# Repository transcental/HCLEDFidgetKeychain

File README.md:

# Hack Club LED Fidget Keychain

For my [Solder](https://solder.hackclub.com) project, I decided to make a keychain that has LEDs arranged into the Hack Club "h" logo. The LEDs turn on when it gets dark, and turn off when it's light, using a photoresistor. The design also features a button controller vibration motor for maximum fidgeting ability.

## Parts List
- 1x PCB
- 6x LEDs
- 6x 220Ω resistors
- 3x 4.7kΩ resistors
- 1x Photoresistor
- 1x Push button
- 1x Vibration motor
- 1x CR2032 battery holder
- 1x CR2032 battery
- 1x NPN transistor

## Images

### Schematic

### PCB

### 3D Model

_Made by Amber - @transcental on Slack_

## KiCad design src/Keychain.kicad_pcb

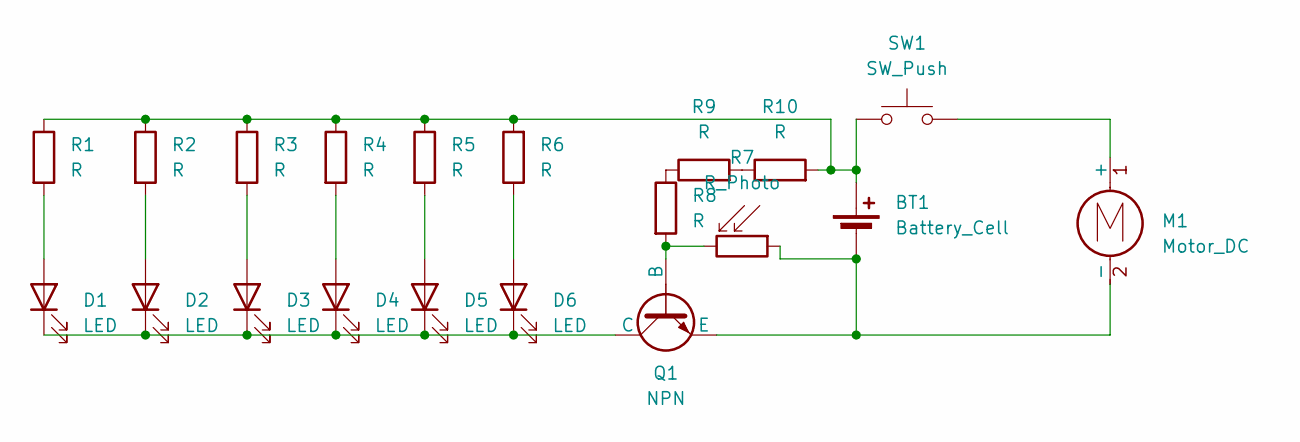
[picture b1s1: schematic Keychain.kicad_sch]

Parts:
BT1: Battery_Cell; BatteryHolder_Keystone_3034_1x20mm
D1, D2, D3, D4, D5, D6: LED; LED_D5.0mm
M1: Motor_DC; PinHeader_2x01_P2.54mm_Vertical
Q1: NPN; TO-92L_HandSolder
R1, R2, R3, R4, R5, R6, R8, R9, R10: R; R_Axial_DIN0207_L6.3mm_D2.5mm_P7.62mm_Horizontal
R7: R_Photo; R_LDR_5.1x4.3mm_P3.4mm_Vertical
SW1: SW_Push; SW_PUSH_6mm

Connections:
unnamed: BT1.1 (+), R1.1, R2.1, R3.1, R4.1, R5.1, R6.2, R10.2, SW1.1
unnamed: BT1.2 (-), M1.2 (-), Q1.3 (E), R7.1
unnamed: D1.2 (A), R1.2
unnamed: D1.1 (K), D2.1 (K), D3.1 (K), D4.1 (K), D5.1 (K), D6.1 (K), Q1.1 (C)
unnamed: D2.2 (A), R2.2
unnamed: D3.2 (A), R3.2
unnamed: D4.2 (A), R4.2
unnamed: D5.2 (A), R5.2
unnamed: D6.2 (A), R6.1
unnamed: M1.1 (+), SW1.2
unnamed: Q1.2 (B), R7.2, R8.2
unnamed: R8.1, R9.1
unnamed: R9.2, R10.1

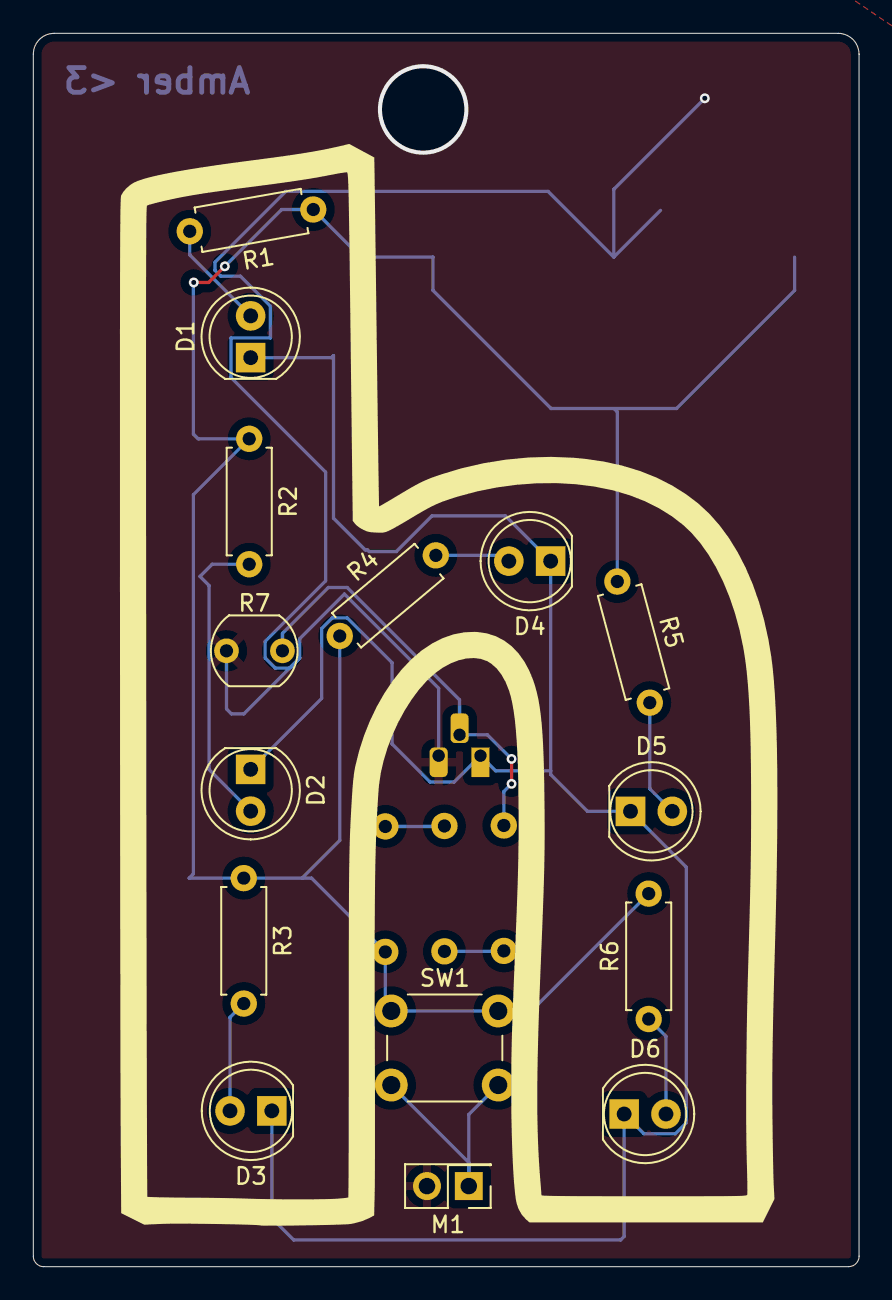
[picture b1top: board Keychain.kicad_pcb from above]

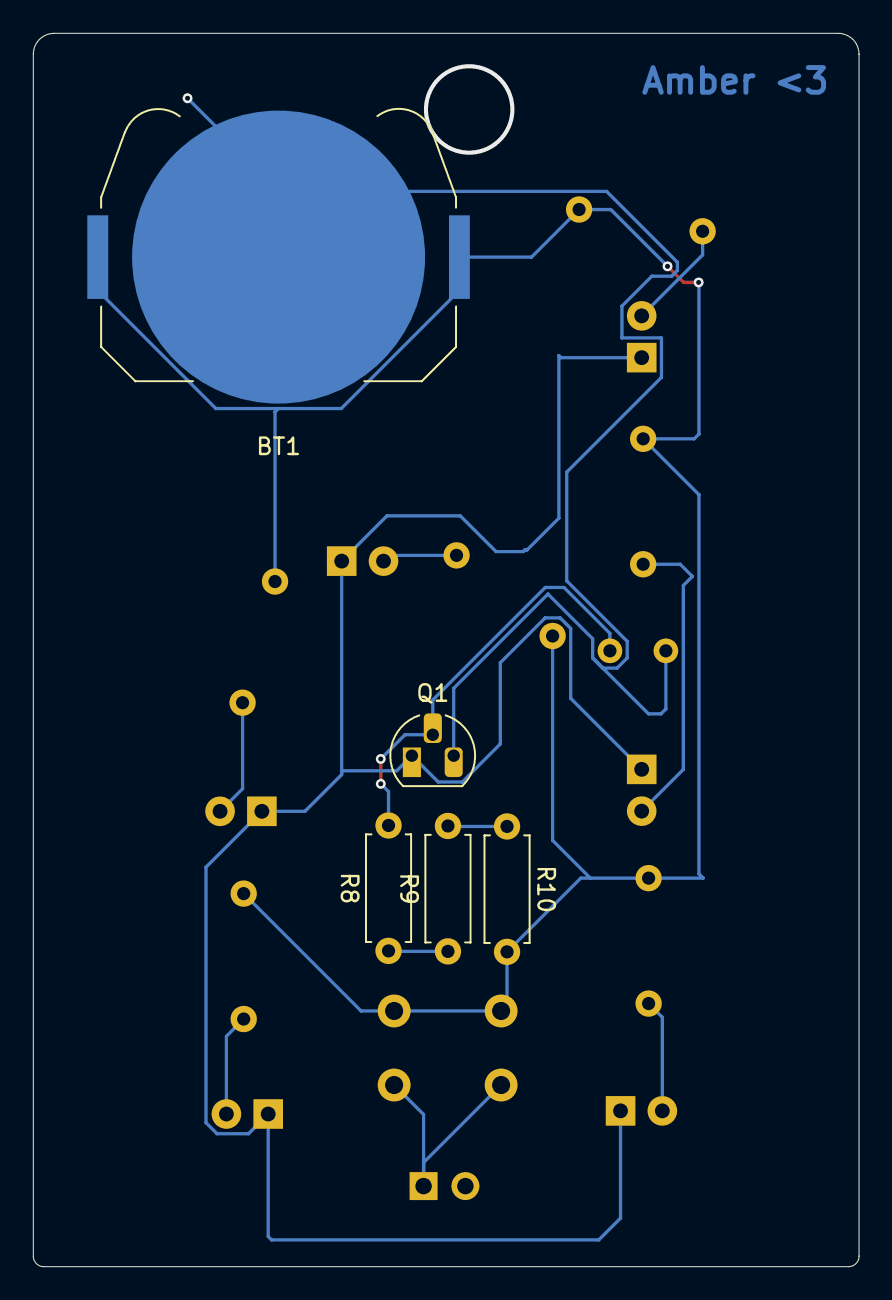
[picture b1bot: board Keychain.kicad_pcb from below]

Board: 2 copper layers, 50.2 x 74.9 mm, 20 parts (5 on the bottom side), 13 nets.

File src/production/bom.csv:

Designator,Footprint,Quantity,Value,LCSC Part #
BT1,BatteryHolder_Keystone_3034_1x20mm,1,Battery_Cell,
"D1, D2, D3, D4, D5, D6",LED_D5.0mm,6,LED,
M1,PinHeader_2x01_P2.54mm_Vertical,1,Motor_DC,
Q1,TO-92L_HandSolder,1,NPN,
"R1, R10, R2, R3, R4, R5, R6, R8, R9",R_Axial_DIN0207_L6.3mm_D2.5mm_P7.62mm_Horizontal,9,R,
R7,R_LDR_5.1x4.3mm_P3.4mm_Vertical,1,R_Photo,
SW1,SW_PUSH_6mm,1,SW_Push,

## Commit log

2025-05-15 add project
2025-05-15 rounded corners!
2025-05-15 idk, i didn't save?
